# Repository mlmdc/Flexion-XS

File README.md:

<h1 align="center">Flexion XS</h1>

<p align="left">
  <strong>🇬🇧 EN - </strong> Measure the vibrations of a bending beam and compare its observed frequencies and mode shapes with a mechanical model.<br>
  <strong>🇫🇷 FR - </strong> Mesurer les vibrations d’une réglette en flexion et confronter les fréquences et modes observés à un modèle mécanique.
</p>

[Retour au portfolio / Back to portfolio](https://mlmdc.github.io/mlmdc_portfolio/) · [Sommaire / Contents](#sommaire--contents)
</div>

## Sommaire / Contents

- [Présentation / Overview](#présentation--overview)
- [Problématique et approche / Problem & approach](#problématique-et-approche--problem--approach)
- [Choix techniques / Technical decisions](#choix-techniques--technical-decisions)
- [Résultats et apprentissages / Results & learnings](#résultats-et-apprentissages--results--learnings)
- [Getting started](#getting-started)
- [Organisation du dépôt / Repository layout](#organisation-du-dépôt--repository-layout)

## Présentation / Overview

🇫🇷 **FR -** Flexion XS est une plateforme expérimentale pédagogique consacrée aux vibrations d’une réglette assimilée à une poutre. Une carte STM32 acquiert l’accélération d’un accéléromètre analogique et la vitesse d’un moteur ; un programme Python permet de commander la maquette et de recevoir les mesures. Les notebooks exploitent ensuite des mesures en plusieurs points pour étudier les fréquences propres, les formes modales et l’amortissement, et les comparer à un modèle de poutre.

Le dépôt s’adresse aux étudiants et aux personnes qui reprennent le projet : il rassemble le firmware, l’outil de mesure, des données, des analyses et les documents de conception. Une acquisition en direct nécessite la maquette et sa carte STM32.
<br>
🇬🇧 **EN -** Flexion XS is an educational experimental platform for studying the vibrations of a beam-like strip. An STM32 board samples an analog accelerometer and reads motor speed; a Python program controls the rig and receives measurements. Notebooks then use measurements taken at several positions to study natural frequencies, mode shapes and damping, and compare them with a beam model.

The repository is intended for students and project maintainers. It contains the firmware, measurement tools, sample data, analysis notebooks and design documents. Live acquisition requires the physical rig and its STM32 board.

### Fonctionnalités / Features

- 🇫🇷 **FR :** acquisition de l’accélération et de la vitesse du moteur ; commandes série pour la maquette ; export des mesures ; analyses des régimes libre et harmonique.
- 🇬🇧 **EN :** accelerometer and motor-speed acquisition; serial commands for the rig; measurement export; free-response and harmonic-analysis notebooks.

## Problématique et approche / Problem & approach

🇫🇷 **FR -** L’objectif est de caractériser la réponse vibratoire d’une réglette instrumentée, puis de confronter les observations à un modèle mécanique. Une mesure doit associer l’évolution temporelle de l’accélération aux positions d’observation et, en régime forcé, à l’excitation produite par le moteur. La chaîne mise en place va du capteur analogique à la STM32, puis à l’enregistrement Python et au post-traitement hors ligne.

Pour le régime libre, les notebooks calculent les réponses fréquentielles à partir des mesures d’accélération et estiment les fréquences et amortissements modaux, notamment par sélection de pics à −3 dB et ajustement de cercles. Les formes modales expérimentales sont comparées à celles d’un modèle éléments finis de poutre, avec notamment un critère MAC. Un notebook distinct étudie la réponse harmonique par superposition modale.

<br>

🇬🇧 **EN -** The aim is to characterize the vibration response of an instrumented beam and compare the observations with a mechanical model. A measurement must relate acceleration over time to the observation positions and, in forced response, to the excitation generated by the motor. The implemented chain runs from the analog sensor through the STM32 to Python recording and offline analysis.

For free response, the notebooks derive frequency-response functions from acceleration measurements and estimate modal frequencies and damping, including peak picking at −3 dB and circle fitting. Experimental mode shapes are compared with those from a finite-element beam model, including with the Modal Assurance Criterion (MAC). A separate notebook studies harmonic response using modal superposition.

## Choix techniques / Technical decisions

🇫🇷 **FR :**
- **STM32F411 et HAL en C :** la carte regroupe l’acquisition ADC, l’encodeur moteur, la commande PWM et la liaison série. Le DMA et les interruptions périodiques limitent le travail bloquant pendant l’acquisition.
- **Accéléromètre analogique et encodeur :** ils permettent d’observer la réponse de la réglette et la vitesse d’excitation avec l’électronique disponible. L’acquisition actuelle repose sur un seul canal d’accéléromètre.
- **UART à 921600 bauds et trames texte :** le format délimité facilite l’inspection et l’exploitation depuis Python. Ce choix simple impose toutefois une charge de transmission et une synchronisation à surveiller.
- **Python, NumPy, SciPy et notebooks :** séparer la mesure du post-traitement permet d’explorer les méthodes sans modifier le firmware. Les analyses gardent des plages de sélection et paramètres manuels ; elles ne constituent donc pas un pipeline entièrement automatisé.
- **Modèle éléments finis :** les notebooks utilisent un modèle de poutre d’Euler–Bernoulli discrétisé, utile pour confronter fréquences et formes modales, mais qui repose sur des hypothèses simplificatrices par rapport à la maquette réelle.

<br>

🇬🇧 **EN :**
- **STM32F411 and C HAL:** the board handles ADC acquisition, the motor encoder, PWM control and serial communication. DMA and periodic interrupts reduce blocking work during acquisition.
- **Analog accelerometer and encoder:** these components measure the beam response and excitation speed using the available electronics. The current acquisition uses a single accelerometer channel.
- **921600-baud UART and text frames:** delimited values are straightforward to inspect and process in Python, at the cost of transmission overhead and synchronization constraints.
- **Python, NumPy, SciPy and notebooks:** separating acquisition from post-processing allows analysis methods to be explored without changing the firmware. The analyses use manually selected ranges and parameters, so they are not a fully automated pipeline.
- **Finite-element model:** the notebooks use a discretized Euler–Bernoulli beam model to compare frequencies and mode shapes. It simplifies the physical rig and its boundary conditions.

## Résultats et apprentissages / Results & learnings

<p><em>FR : Décroissance de l’accélération après l’excitation. <br> EN: Acceleration decay after excitation.</em></p>

<p><em>FR : Réponses fréquentielles mesurées en trois positions. <br> EN: Frequency responses measured at three positions.</em></p>

<p><em>FR : Comparaison des formes modales mesurées et modélisées. <br> EN: Comparison of measured and modeled mode shapes.</em></p>

🇫🇷 **FR -** Le dépôt contient trois séries de mesures (`P1FRF.csv`, `P2FRF.csv`, `P3FRF.csv`) et des notebooks qui produisent des réponses fréquentielles et des comparaisons modales. Les fichiers documentent une chaîne expérimentale et des méthodes d’analyse utilisables comme base de travail ; ils ne suffisent pas, à eux seuls, à établir une validation quantitative du modèle ou une précision générale des estimations.

Les documents du projet signalent plusieurs limites encore ouvertes : le troisième mode en régime libre reste à mieux identifier, l’ajustement des cercles et le traitement doivent gagner en répétabilité, et des problèmes d’intégration électrique (notamment de masses) compliquent l’utilisation de la maquette. Le firmware et le protocole série nécessitent également une vérification avant de considérer l’acquisition comme robuste. Les évolutions proposées comprennent la fiabilisation du câblage et de la communication, une acquisition multi-capteurs et des essais répétés avec paramètres et conditions consignés.

<br>

🇬🇧 **EN -** The repository includes three measurement series (`P1FRF.csv`, `P2FRF.csv`, `P3FRF.csv`) and notebooks that compute frequency responses and compare mode shapes. They document an experimental workflow and analysis methods that can be extended; by themselves, they do not establish quantitative model validation or general accuracy of the estimates.

The project documents identify open limitations: the third free-response mode needs better identification, circle fitting and data processing need to be more repeatable, and electrical integration issues—particularly grounding—complicate use of the rig. The firmware and serial protocol also need verification before acquisition can be considered robust. Proposed next steps include improving wiring and communication reliability, adding sensor channels, and repeating experiments while recording parameters and test conditions.

## Getting started

The commands below install the Python packages used by the measurement and analysis notebooks. Run them from the repository root.

```mermaid
flowchart LR
    subgraph Acquisition["Live measurement"]
        Rig["Beam, accelerometer<br/>and motor"] --> STM32["STM32<br/>sample acceleration<br/>read motor speed"]
        STM32 -->|UART, 921600 baud| Serial["serial_com.ipynb<br/>control and record"]
        Serial --> Data["Measurement CSV files"]
    end

    subgraph Analysis["Offline analysis"]
        Samples["Supplied measurements<br/>or new CSV files"] --> Free["Free-response notebook<br/>frequencies, damping<br/>and mode shapes"]
        Samples --> Harmonic["Harmonic notebook<br/>model response"]
    end

    Data --> Samples
```

The live acquisition path requires the physical rig. The analysis notebooks can also run directly on the supplied measurement files without hardware.

### Prerequisites

- Python 3.10 (the version documented for this project)
- JupyterLab
- For live acquisition: the physical rig, an STM32F411 board, STM32CubeIDE 1.12.0 / CubeMX 6.8.7, and a serial connection

### Install and launch the notebooks

```powershell
python -m venv .venv
.\.venv\Scripts\Activate.ps1
python -m pip install --upgrade pip
python -m pip install jupyterlab numpy matplotlib scipy pyserial
jupyter lab
```

### Analyze the supplied measurements

Open `5_Post-traitements/1_Libre/analyse_modale_flexion_vfinal.ipynb` in JupyterLab and run its cells in order. The notebook reads the three semicolon-delimited files in `Measurements/`. The files contain time and acceleration samples; no live hardware is needed for this analysis.

For the harmonic case, open `5_Post-traitements/2_Harmonique/analyse_harmonique_flexion_v1.ipynb`. Its model parameters and simulation settings are defined in the notebook.

### Acquire a new measurement

Open `REGLETTE_CMV/REGLETTE_CMV.ioc` in STM32CubeIDE and build/flash the firmware. Then open `serial_com.ipynb` and connect to the board's serial port at **921600 baud** before running its acquisition cells. The current notebook's automatic port detection expects a particular ST-Link description; on Windows, set the correct `COM` port if it is not detected. The measurement guide explains the physical setup and operation: [0_Documents/Sources/tutoriel.md](0_Documents/Sources/tutoriel.md).

Check the emergency stop, power wiring and grounding before operating the motor or electromagnet. Hardware measurements are not reproducible from software dependencies alone.

## Organisation du dépôt / Repository layout

| Path | Contents |
| --- | --- |
| `REGLETTE_CMV/` | STM32CubeIDE project, firmware and board configuration |
| `serial_com.ipynb` | PC-side serial connection, commands and measurement workflow |
| `Measurements/` | Three sample acceleration time series and CSV helper |
| `5_Post-traitements/1_Libre/` | Free-response and modal-analysis notebook versions |
| `5_Post-traitements/2_Harmonique/` | Harmonic-response analysis notebook |
| `0_Documents/` | Measurement guide, project documents and their sources |
| `1_Documentation_codes/` | Code documentation and Python serial module requirements |
| `2_Conception_électronique/` | Electronics design files and activity report |
| `3_Conception_Mécanique/` | CAD parts, assembly and 3D-print files |
| `4_Medias/Photos/` | Rig, wiring and analysis images |

## License

This project is licensed under the MIT License. See the [LICENSE](LICENSE) file for details.

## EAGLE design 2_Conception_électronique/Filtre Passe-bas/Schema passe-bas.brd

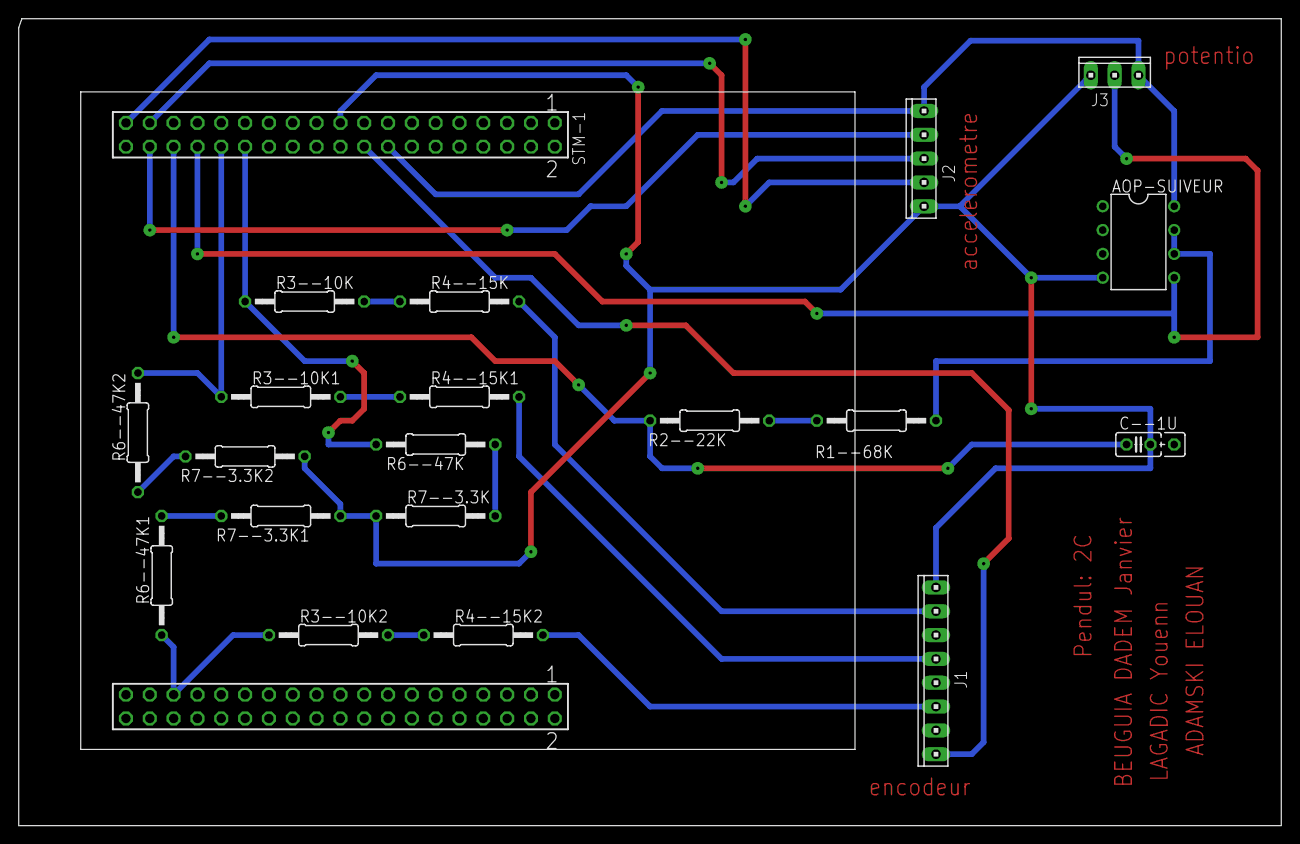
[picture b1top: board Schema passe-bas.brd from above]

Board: 2 copper layers, 134.6 x 86.0 mm, 20 parts (0 on the bottom side), 22 nets.

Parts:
AOP-SUIVEUR: TL082P; DIL08
C--1U: C025_050-025X075
J1: 10X08MTA
J2: 10X05MTA
J3: 10X03MTA
R1--68K, R2--22K, R3--10K, R3--10K1, R3--10K2, R4--15K, R4--15K1, R4--15K2, R6--47K, R6--47K1, R6--47K2, R7--3.3K, R7--3.3K1, R7--3.3K2: 0207/12
STM-1: NUCLEO-F411RE; CONN_STM32_NUCLEO

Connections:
GND: AOP-SUIVEUR.4, C--1U.2, J1.1, J2.5, J3.3, R7--3.3K.1, R7--3.3K1.1, R7--3.3K2.1, STM-1.19
unnamed: R1--68K.2, R2--22K.1
unnamed: AOP-SUIVEUR.6, AOP-SUIVEUR.7, R1--68K.1
unnamed: R3--10K2.1, R6--47K1.1, STM-1.71
unnamed: AOP-SUIVEUR.5, J3.2, STM-1.32
unnamed: R6--47K.1, R7--3.3K.2
unnamed: J1.2, R4--15K.2
unnamed: R3--10K.2, R4--15K.1
unnamed: R6--47K1.2, R7--3.3K1.2
unnamed: R3--10K.1, R6--47K.2, STM-1.28
unnamed: J1.4, R4--15K1.2
unnamed: AOP-SUIVEUR.8, J2.1, J3.1, STM-1.16
unnamed: R3--10K1.2, R4--15K1.1
unnamed: R6--47K2.1, R7--3.3K2.2
unnamed: R3--10K1.1, R6--47K2.2, STM-1.30
unnamed: J1.6, R4--15K2.2
unnamed: R3--10K2.2, R4--15K2.1
unnamed: C--1U.1, R2--22K.2, STM-1.34
unnamed: J2.4, STM-1.37
unnamed: J2.3, STM-1.35
unnamed: J2.2, STM-1.36
VCC: J1.8, STM-1.18
